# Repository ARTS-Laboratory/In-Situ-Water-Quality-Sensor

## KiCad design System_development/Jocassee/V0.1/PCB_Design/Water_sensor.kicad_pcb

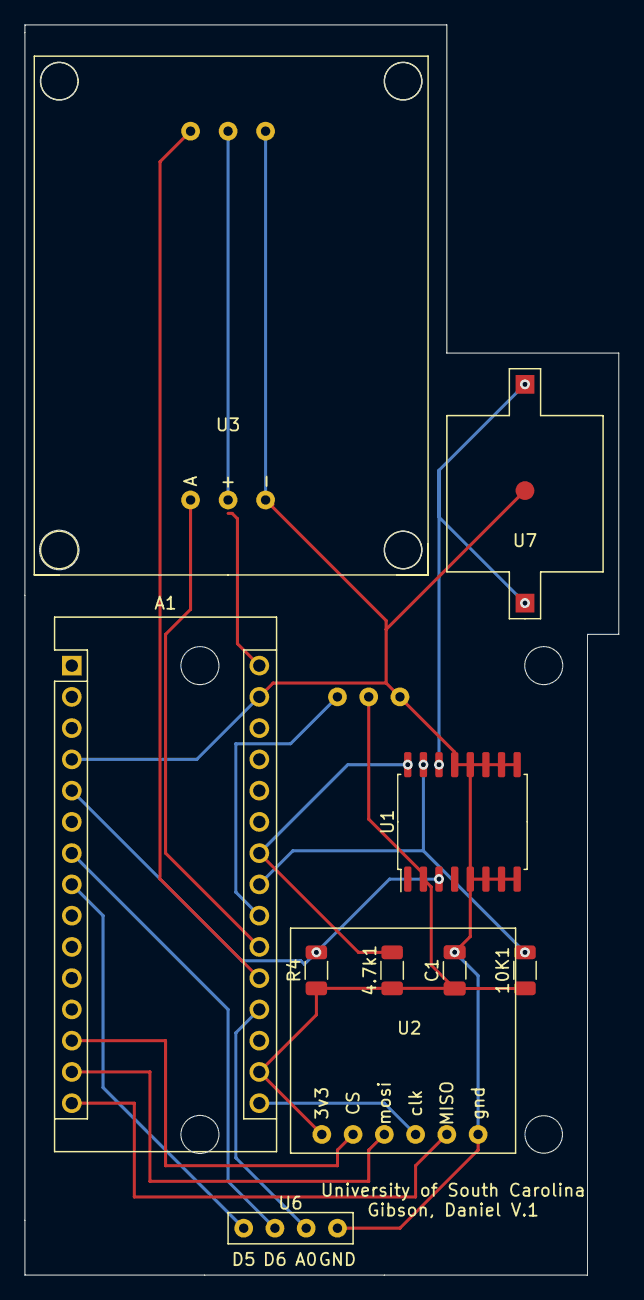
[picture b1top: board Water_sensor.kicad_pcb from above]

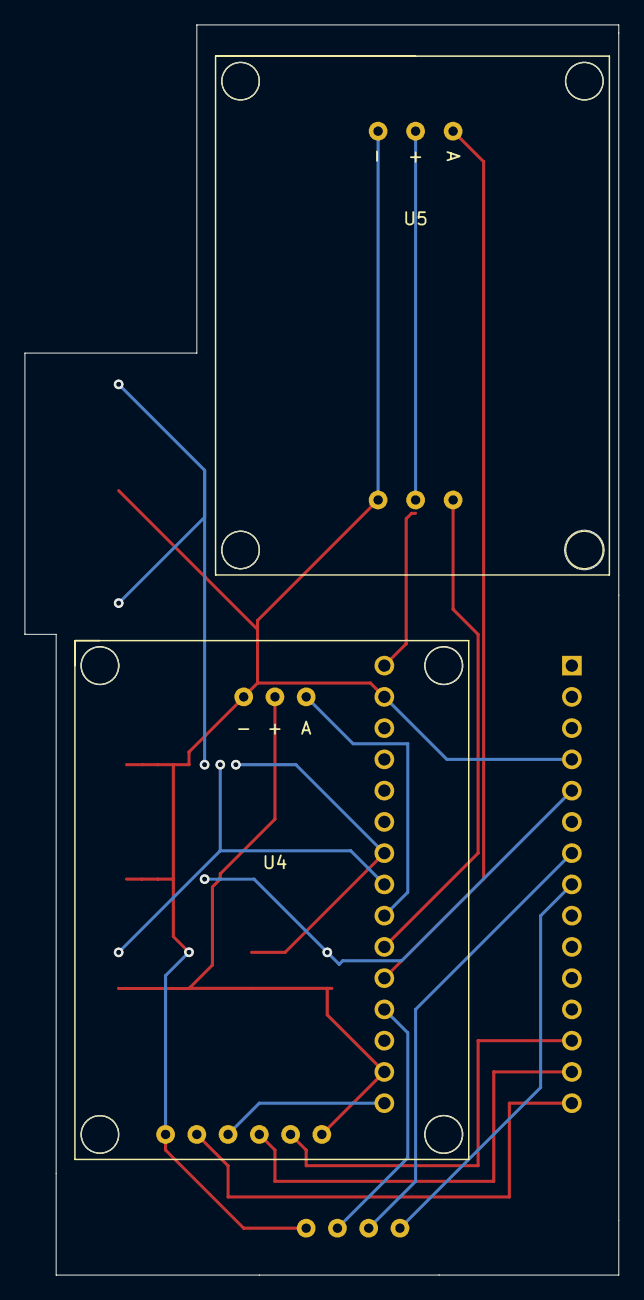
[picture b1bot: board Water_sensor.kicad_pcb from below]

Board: 2 copper layers, 48.3 x 101.6 mm, 12 parts (2 on the bottom side), 17 nets.

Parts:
4.7k1, 10K1: R; R_1206_3216Metric
A1: Arduino_Nano_v3.x; Arduino_Nano
C1: C; C_1206_3216Metric
R4: R; R_1206_3216Metric
U1: DS3231M; SOIC-16W_7.5x10.3mm_P1.27mm
U2: MicroSD.V2
U3: Phsensor; PH_meter
U4: TDSSensor; TDS_meter
U5: ORPmeter; ORP_meter
U6: Rails
U7: CR1025

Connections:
GND: A1.4, A1.29, C1.2, U1.5, U1.6, U1.7, U1.8, U1.9, U1.10, U1.11, U1.12, U1.13, U2.6, U3.3, U4.3, U5.3, U6.4, U7.3
unnamed: 4.7k1.2, A1.24, U1.16
unnamed: 4.7k1.1, 10K1.1, A1.17, C1.1, R4.1, U1.2, U2.1, U4.2
unnamed: 10K1.2, A1.23, U1.15
unnamed: A1.5, R4.2, U1.3
unnamed: A1.7, U6.2
unnamed: A1.8, U6.1
unnamed: A1.13, U2.2
unnamed: A1.14, U2.3
unnamed: A1.15, U2.5
unnamed: A1.16, U2.4
unnamed: A1.19, U6.3
unnamed: A1.20, U5.1
unnamed: A1.21, U3.1
unnamed: A1.22, U4.1
unnamed: A1.27, U3.2, U5.2
unnamed: U1.14, U7.1, U7.2

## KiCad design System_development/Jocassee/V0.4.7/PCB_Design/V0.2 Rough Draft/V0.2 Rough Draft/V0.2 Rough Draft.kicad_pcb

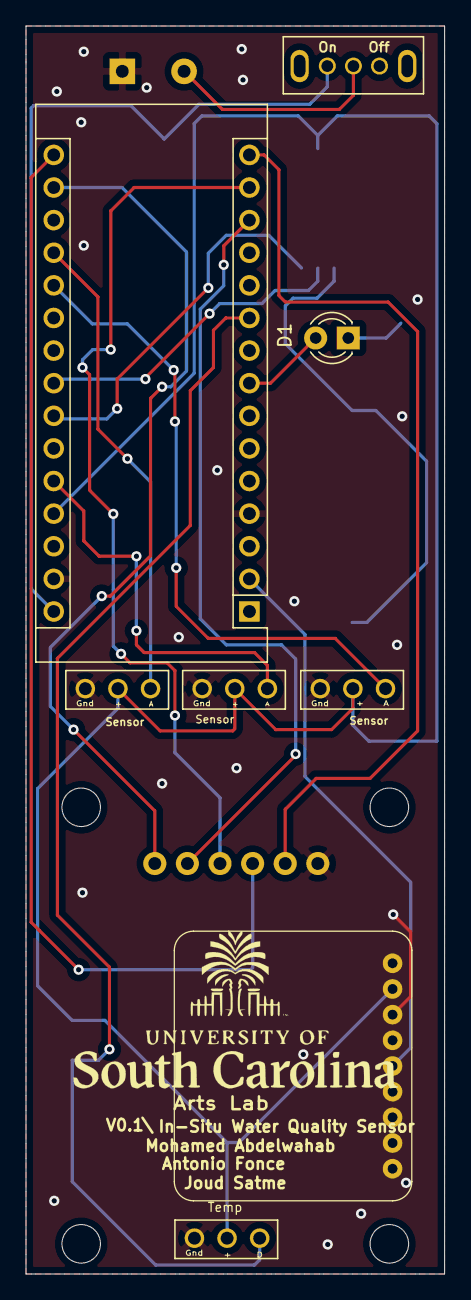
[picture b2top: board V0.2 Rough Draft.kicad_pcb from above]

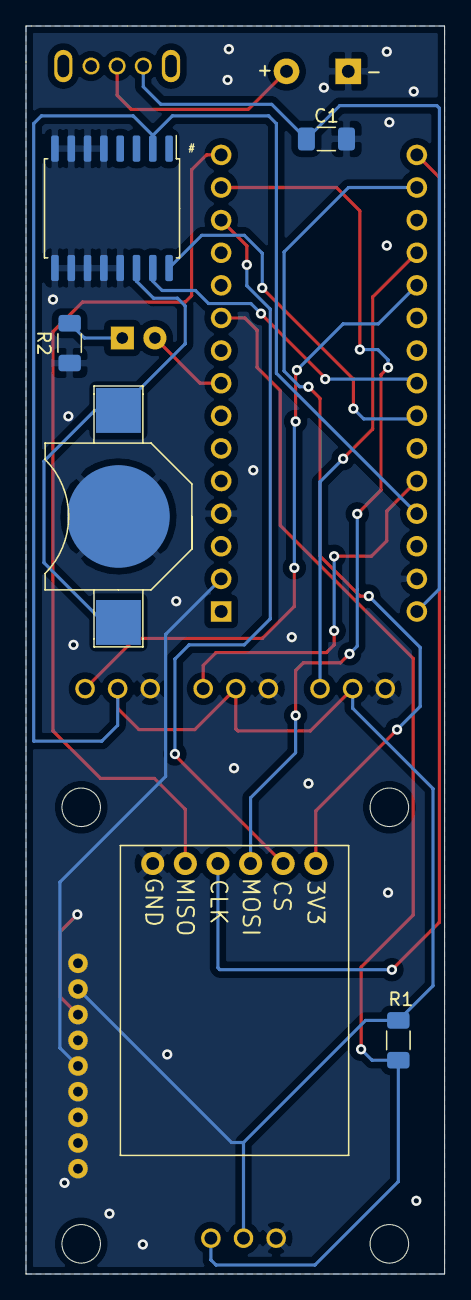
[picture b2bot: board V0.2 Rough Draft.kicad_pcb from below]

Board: 2 copper layers, 32.6 x 97.2 mm, 15 parts (7 on the bottom side), 19 nets.

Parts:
A1: Arduino_Nano_v3.x; Arduino_Nano
BT1: Battery_Cell; battery_holder_10mm
C1: C; C_1206_3216Metric_Pad1.33x1.80mm_HandSolder
D1: LED; LED_D3.0mm
R1, R2: R; R_1206_3216Metric_Pad1.30x1.75mm_HandSolder
U1: water_Battery; Battery_Input
U2: SD
U3: switch; grounded_switch
U4: Sensor; phraails
U5: Sensor; TDS
U6: DS3231M; SOIC-16W_7.5x10.3mm_P1.27mm
U7: Sensor; Turbidity
U8: Temp; Temp.
U9: GPS Module

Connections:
GND: A1.4 (GND), A1.29 (GND), BT1.2 (-), C1.2, R2.2, U1.2 (Gnd), U2.6 (GND), U4.1 (GND), U5.1 (GND), U6.5 (GND), U6.6 (GND), U6.7 (GND), U6.8 (GND), U6.9 (GND), U6.10 (GND), U6.11 (GND), U6.12 (GND), U6.13 (GND), U7.1 (GND), U8.1 (Gnd), U9.7 (GND)
unnamed: A1.17 (3V3), U2.1 (3V)
unnamed: A1.27 (+5V), R1.2, U4.2 (+), U5.2 (+), U6.2 (VCC), U7.2 (+), U8.2 (5V), U9.8 (VIN)
unnamed: A1.19 (A0), U4.3 (A)
unnamed: A1.20 (A1), U5.3 (A)
unnamed: A1.23 (A4), U6.15 (SDA)
unnamed: A1.24 (A5), U6.16 (SCL)
unnamed: A1.26 (A7), U7.3 (A)
unnamed: A1.2 (D0/RX), U9.5 (TX)
unnamed: A1.8 (D5), D1.2 (A)
unnamed: A1.10 (D7), R1.1, U8.3 (D)
unnamed: A1.13 (D10), U2.2 (CS)
unnamed: A1.14 (D11), U2.3 (Mosi)
unnamed: A1.15 (D12), U2.5 (Miso)
unnamed: A1.16 (D13), U2.4 (CLK)
unnamed: A1.30 (VIN), C1.1, U3.3 (PO)
unnamed: BT1.1 (+), U6.14 (VBAT)
unnamed: D1.1 (K), R2.1
unnamed: U1.1 (Power), U3.2 (PI)

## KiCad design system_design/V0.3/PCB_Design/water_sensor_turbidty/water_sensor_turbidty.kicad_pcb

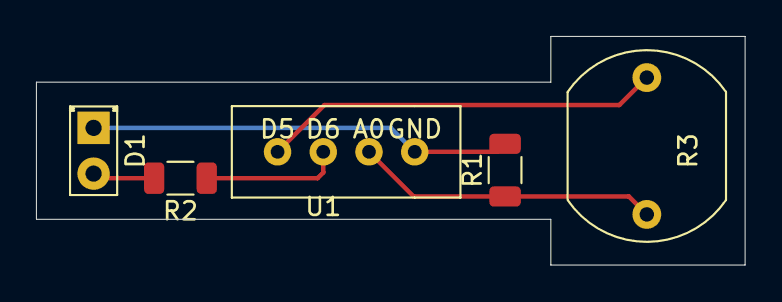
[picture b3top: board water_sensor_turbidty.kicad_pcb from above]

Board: 2 copper layers, 39.4 x 12.7 mm, 5 parts (0 on the bottom side), 5 nets.

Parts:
D1: LED; LED_D2.0mm_W4.8mm_H2.5mm_FlatTop
R1: 1K; R_1206_3216Metric
R2: 470; R_1206_3216Metric
R3: LDR03; R_LDR_10x8.5mm_P7.6mm_Vertical
U1: railsforturbity; Rails

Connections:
unnamed: D1.1, R1.2, U1.4
unnamed: D1.2, R2.2
unnamed: R1.1, R3.2, U1.3
unnamed: R2.1, U1.2
unnamed: R3.1, U1.1

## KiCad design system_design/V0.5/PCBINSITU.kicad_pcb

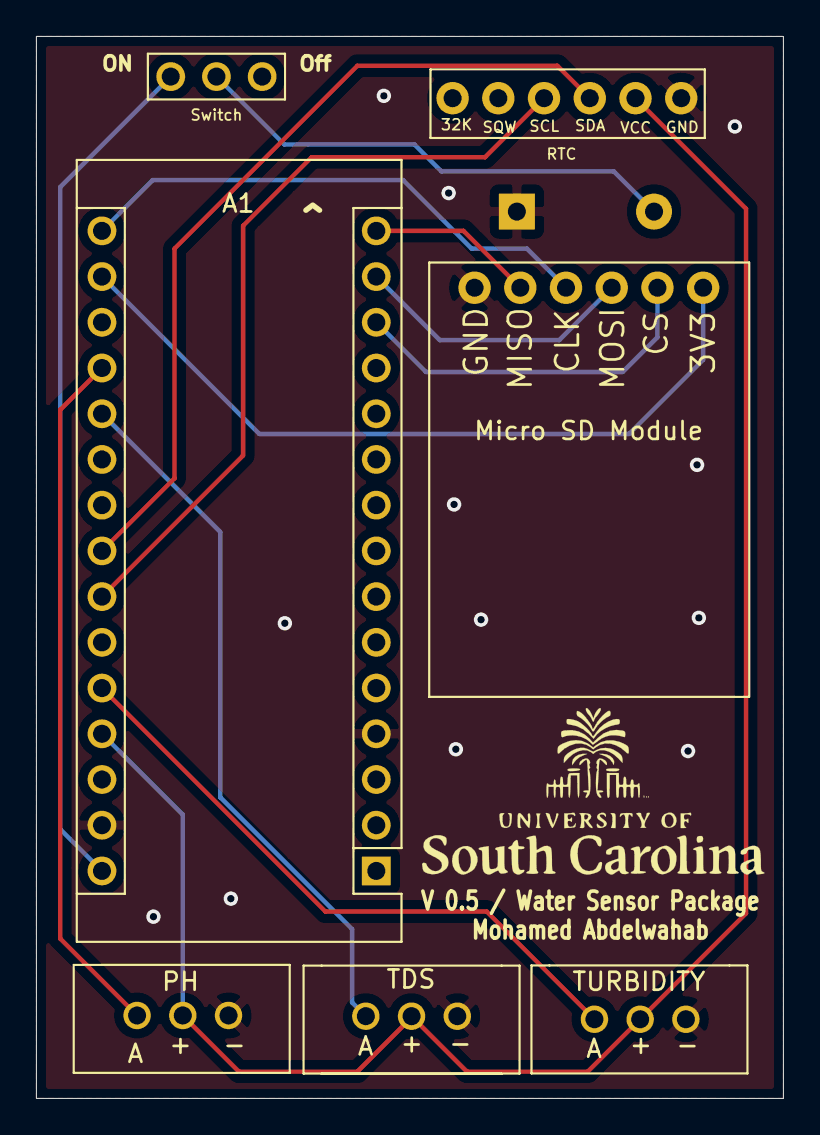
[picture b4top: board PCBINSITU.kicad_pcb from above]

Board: 2 copper layers, 41.5 x 59.0 mm, 8 parts (1 on the bottom side), 14 nets.

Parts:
A1: Arduino_Nano_v3.x; Arduino_Nano
U1: SD
U2: BATTERY; Battery_Input
U3: SWITCH; slide_switch
U4: TURBIDITY; turbidity_rails
U5: PH; phraails
U6: TDS; sensor_rails
U7: RTC; SD Module

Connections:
GND: A1.4, A1.29, U1.6, U2.2, U4.3, U5.3, U6.3, U7.6
unnamed: A1.13, U1.2
unnamed: A1.14, U1.3
unnamed: A1.15, U1.5
unnamed: A1.16, U1.4
unnamed: A1.17, U1.1
unnamed: A1.19, U5.1
unnamed: A1.20, U6.1
unnamed: A1.23, U7.4
unnamed: A1.24, U7.3
unnamed: A1.26, U4.1
unnamed: A1.27, U4.2, U5.2, U6.2, U7.5
unnamed: A1.30, U3.3
unnamed: U2.1, U3.2
